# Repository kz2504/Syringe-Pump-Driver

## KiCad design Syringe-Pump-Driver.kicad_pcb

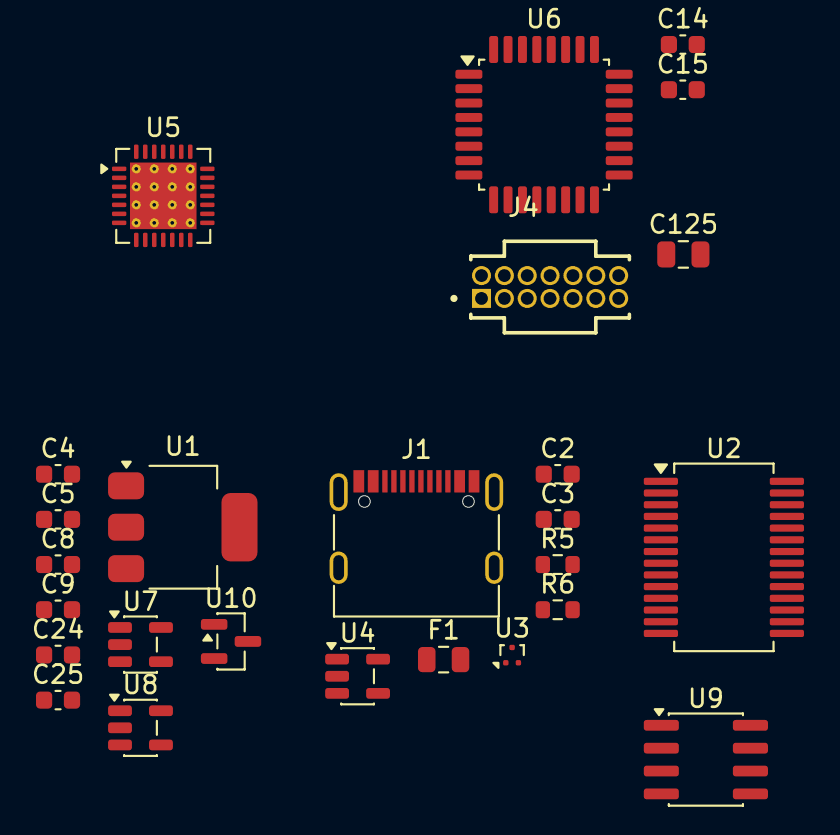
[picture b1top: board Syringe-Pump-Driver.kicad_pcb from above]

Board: 2 copper layers, 26 parts (0 on the bottom side), 22 nets, no tracks yet.

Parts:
C2, C3, C4, C5, C8, C9, C14, C15, C24, C25: 1uF; C_0603_1608Metric
C125: 0.1uF; C_0805_2012Metric
F1: 500mA; Fuse_0805_2012Metric
J1: USB_C_Receptacle_USB2.0_16P; USB_C_Receptacle_G-Switch_GT-USB-7010ASV
J4: FTSH-107-01-L-D-K; SAMTEC_FTSH-107-01-L-D-K
R5, R6: 5.1K; R_0603_1608Metric
U1: LD1117S50TR_SOT223; SOT-223-3_TabPin2
U2: FT232RL; SSOP-28_5.3x10.2mm_P0.65mm
U3: TPD2EUSB30; Texas_DRT-3
U4, U7: MAX40200AUK; SOT-23-5
U5: TMC2209-LA; VQFN-28-1EP_5x5mm_P0.5mm_EP3.7x3.7mm_ThermalVias
U6: STM32G431KBTx; LQFP-32_7x7mm_P0.8mm
U8: AP2127K-3.3; SOT-23-5
U9: MCP2562-E-SN; SOIC-8_3.9x4.9mm_P1.27mm
U10: MCP1700x-150xxTT; SOT-23

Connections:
+1V5: C25.2, U10.2 (VO)
+3.3V: C125.1, J4.03
+3V3: C5.2, U2.4 (VCCIO), U5.15 (VCC_IO), U6.1 (VDD), U6.17 (VDD), U8.5 (VOUT), U9.5 (Vio)
+5V: C3.2, C4.2, C24.2, U2.20 (VCC), U4.5 (OUT), U7.5 (OUT), U8.1 (VIN), U8.3 (EN), U9.3 (VDD), U10.3 (VI)
+12V: C8.2, U1.3 (VI), U5.22 (VS), U5.28 (VS)
/CAN/FDCAN1_RX: U6.21 (PA11), U9.4 (RXD)
/CAN/FDCAN1_TX: U6.22 (PA12), U9.1 (TXD)
/MCU/NRST: J4.12, U6.4 (PG10)
/MCU/SWCLK: J4.06, U6.24 (PA14)
/MCU/SWDIO: J4.04, U6.23 (PA13)
/MCU/USART1_RX: U2.1 (TXD), U6.20 (PA10)
/MCU/USART1_TX: U2.5 (RXD), U6.19 (PA9)
/USB-UART/D+: J1.A6 (D+), J1.B6 (D+), U2.15 (USBD+), U3.1 (D+)
/USB-UART/D-: J1.A7 (D-), J1.B7 (D-), U2.16 (USBD-), U3.2 (D-)
GND: C2.1, C3.1, C4.1, C5.1, C8.1, C9.1, C14.2, C15.1, C24.1, C25.1, C125.2, J1.A1 (GND), J1.A12 (GND), J1.B1 (GND), J1.B12 (GND), J1.S1 (SHIELD), J4.05, J4.07, J4.11, R5.2, R6.2, U1.1 (GND), U2.7 (GND), U2.18 (GND), U2.21 (GND), U2.25 (AGND), U2.26 (TEST), U3.3 (GND), U4.2 (GND), U5.3 (GND), U5.13 (CLK), U5.18 (GND), U5.25 (NC), U5.29 (GND), U6.14 (VSSA), U6.16 (VSS), U6.32 (VSS), U7.2 (GND), U8.2 (GND), U9.2 (VSS), U9.8 (STBY), U10.1 (GND)
unnamed: F1.1, J1.A4 (VBUS), J1.A9 (VBUS), J1.B4 (VBUS), J1.B9 (VBUS)
unnamed: J1.A5 (CC1), R5.1
unnamed: J1.B5 (CC2), R6.1
unnamed: C9.2, U1.2 (VO), U7.1 (VDD), U7.3 (EN)
unnamed: C2.2, F1.2, U4.1 (VDD), U4.3 (EN)
unnamed: C14.1, U6.2 (PF0)
unnamed: C15.2, U6.3 (PF1)

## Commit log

2026-06-01 test
